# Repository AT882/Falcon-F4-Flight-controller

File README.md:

# Falcon F4 Flight Controller

Custom STM32F405-based flight controller designed for UAV, FPV and aerial robotics applications.

## Overview

The Falcon F4 Flight Controller is a custom-designed flight-control board based on the STM32F405RGT6 ARM Cortex-M4 microcontroller.

The board integrates the core hardware required for a compact UAV flight-control system, including a 6-axis IMU, barometric pressure sensor, analog video OSD, external SPI Flash memory, regulated power supplies, battery-voltage monitoring, current sensing, ESC interfaces, camera and VTX interfaces, USB connectivity and SWD debugging.

The complete electrical schematic is provided in this repository along with images of the designed PCB.

## Hardware Images

### PCB Front View

### PCB Back View

## Key Features

* STM32F405RGT6 ARM Cortex-M4 microcontroller
* ICM-42688-P 6-axis IMU
* BMP388 barometric pressure sensor
* AT7456E analog OSD controller
* W25Q128JV 128-Mbit SPI NOR Flash
* TPS54202DDCR 5 V buck regulator
* XC6206P332MR 3.3 V LDO regulator
* USB Type-C interface
* SWD programming and debugging interface
* Dedicated boot-mode selection
* Multiple ESC signal outputs
* ESC telemetry interface
* Analog camera input
* Analog VTX output
* Battery-voltage monitoring
* Current-sense input
* SPI interfaces
* I²C interface
* Status LEDs
* Power indication
* Dedicated MCU and OSD clock sources

## Main Processing Unit

### STM32F405RGT6

The STM32F405RGT6 is the main processing unit of the Falcon F4.

It provides the processing capability required for real-time flight-control applications and interfaces with the onboard sensors, memory, OSD circuitry, external peripherals and flight-control interfaces.

The MCU provides connections for:

* IMU
* Barometer
* SPI Flash
* OSD
* ESC interfaces
* Battery-voltage monitoring
* Current sensing
* I²C peripherals
* USB
* SWD
* Status LEDs
* Auxiliary GPIO

## Inertial Measurement Unit

### ICM-42688-P

The ICM-42688-P is used as the primary inertial measurement unit.

It provides:

* 3-axis accelerometer
* 3-axis gyroscope

The IMU is connected to the STM32 through an SPI interface.

The main IMU signals are:

```text
SPI1_SCK
SPI1_MISO
SPI1_MOSI
IMU_CS
```

The IMU has local decoupling capacitors to provide a stable supply and reduce supply noise.

The sensor provides motion information required for:

* Attitude estimation
* Angular-rate measurement
* Flight stabilization
* Orientation estimation
* Flight-control algorithms

## Barometric Pressure Sensor

### BMP388

The BMP388 is used for barometric pressure and altitude measurement.

The sensor is connected to the STM32 through the I²C interface.

The primary signals are:

```text
I2C1_SCL
I2C1_SDA
```

The barometer can be used for:

* Altitude estimation
* Altitude hold
* Vertical-position estimation
* Flight stabilization
* Autonomous UAV applications

## On-Screen Display

### AT7456E

The AT7456E is used as the analog video OSD controller.

The OSD section allows flight information to be overlaid onto the analog video stream.

The video path is:

```text
Camera
   |
   v
AV_IN
   |
   v
AT7456E
   |
   v
AV_OUT
   |
   v
VTX
```

The OSD section includes a dedicated 27 MHz crystal and associated circuitry.

Possible OSD information includes:

* Battery voltage
* Flight mode
* Altitude
* Flight status
* Warnings
* Navigation information
* Telemetry information
* Artificial horizon

## External Flash Memory

### W25Q128JV

The W25Q128JV is a 128-Mbit SPI NOR Flash memory device.

The external Flash provides non-volatile memory for storing application data.

Potential uses include:

* Configuration data
* Parameters
* Logging
* Flight data
* Application-specific information

The Flash interface uses:

```text
FLASH_CS
SPI3_SCK
SPI3_MISO
SPI3_MOSI
```

## Power Management

The Falcon F4 contains dedicated power-management circuitry for generating the required voltage rails.

The main power architecture consists of:

```text
+BATT
   |
   +------------------+
   |                  |
   v                  v
5 V Buck          Battery
Regulator         Monitoring
   |
   v
  5 V
   |
   v
3.3 V LDO
   |
   v
 3.3 V
```

## 5 V Regulator

### TPS54202DDCR

The TPS54202DDCR is used as the primary 5 V switching regulator.

The regulator converts the battery input into a regulated 5 V supply.

The regulator section includes:

* TPS54202DDCR
* Inductor
* Input capacitors
* Output capacitors
* Feedback network
* Enable circuitry
* Power flag

The 5 V rail supplies the OSD/video section and other peripherals requiring 5 V.

## 3.3 V Regulator

### XC6206P332MR

The XC6206P332MR provides the 3.3 V supply rail.

The 3.3 V rail powers the main low-voltage digital and sensor circuitry, including:

* STM32F405RGT6
* ICM-42688-P
* BMP388
* W25Q128JV
* Other 3.3 V peripherals

Local decoupling capacitors are provided for the regulator and individual ICs.

## Battery Voltage Monitoring

The Falcon F4 includes an onboard battery-voltage sensing circuit.

A resistor-divider network scales the battery voltage to a suitable level for the STM32 ADC.

The schematic uses:

```text
R18 = 20 kΩ
R19 = 1 kΩ
```

The scaled signal is connected to:

```text
ADC_IN8
```

This allows the flight-control firmware to monitor the connected battery voltage.

Battery-voltage monitoring can be used for:

* Battery status
* Low-voltage warnings
* Battery protection
* Flight telemetry
* Battery monitoring

## Current Monitoring

A dedicated current-sense input is provided.

The signal is labelled:

```text
CURRENT
```

and is connected to the STM32 ADC system.

The current measurement can be used for:

* Current monitoring
* Power-consumption estimation
* Battery monitoring
* Energy-consumption calculation
* Telemetry
* Low-battery management

The actual current-sensor implementation depends on the external ESC or power-monitoring hardware connected to the flight controller.

## ESC Interface

The Falcon F4 provides a dedicated multi-pin ESC interface.

The schematic includes:

```text
ESC_S1
ESC_S2
ESC_S3
ESC_S4
ESC_S5
ESC_S6
ESC_TLM
CURRENT
+BATT
GND
```

The interface is intended to connect the flight controller to external electronic speed controllers.

The multiple ESC signal connections allow the board to be adapted for different multirotor configurations.

The ESC interface can be used for:

* Motor-control signals
* ESC telemetry
* Current monitoring
* Battery monitoring

The exact communication protocol is determined by the flight-control firmware and connected ESC hardware.

## Camera Interface

A dedicated analog camera interface is provided.

The camera connector includes:

```text
GND
+5V
AV_IN
```

The camera video signal is routed to the AT7456E OSD section.

The OSD then overlays flight information onto the video stream before sending it to the VTX.

## VTX Interface

A dedicated VTX connector is provided.

The interface includes:

```text
GND
+BATT
AV_OUT
VTX_TBS
```

The processed analog video signal is available through:

```text
AV_OUT
```

The VTX control signal can be used with compatible video transmitters and firmware.

## USB Type-C Interface

The Falcon F4 includes a USB Type-C connector.

The USB section includes the required USB-C CC resistors and connections to the STM32.

The interface can be used for:

* Firmware development
* Configuration
* Data communication
* Firmware updates
* Development and testing

## Debugging and Programming

### SWD

A dedicated Serial Wire Debug interface is provided for programming and debugging the STM32F405.

The primary SWD signals are:

```text
SWDIO
SWCLK
```

The SWD interface can be used with an ST-LINK or compatible debugger.

It supports:

* Firmware programming
* Breakpoint debugging
* Register inspection
* Memory inspection
* Peripheral debugging
* Hardware bring-up

## Boot Mode

The board includes a dedicated boot-selection circuit.

The schematic provides:

```text
BOOT
BOOT0
```

along with a boot switch and associated pull-down circuitry.

This allows the MCU boot configuration to be selected during development and firmware recovery.

## Status LEDs

The Falcon F4 includes onboard status and power indication LEDs.

The schematic contains:

```text
LED1
LED2
POWER
```

These LEDs can be assigned by firmware to indicate:

* Power status
* Boot status
* Sensor initialization
* Flight-controller state
* Communication status
* Error conditions

## Clock Sources

The board contains dedicated clock sources for the MCU and OSD subsystem.

### MCU Clock

An 8 MHz crystal is provided for the STM32F405 clock system.

### OSD Clock

A separate 27 MHz crystal is provided for the AT7456E OSD controller.

## Communication Interfaces

### SPI

Multiple SPI interfaces are used for high-speed peripheral communication.

The SPI interfaces are used for devices including:

* ICM-42688-P
* W25Q128JV
* Other external peripherals

### I²C

The board provides an I²C interface for peripheral communication.

The primary signals are:

```text
I2C1_SCL
I2C1_SDA
```

The onboard BMP388 is connected through this interface.

## Major Components

| Reference | Component           | Function                      |
| --------- | ------------------- | ----------------------------- |
| U1        | STM32F405RGT6       | Main flight-controller MCU    |
| U2        | BMP388              | Barometric pressure sensor    |
| U3        | ICM-42688-P         | 6-axis IMU                    |
| U4        | W25Q128JV           | 128-Mbit SPI Flash            |
| U5        | TPS54202DDCR        | 5 V buck regulator            |
| U6        | XC6206P332MR        | 3.3 V LDO regulator           |
| IC1       | AT7456E             | Analog OSD controller         |
| Y1        | 27 MHz crystal      | OSD clock source              |
| Y2        | 8 MHz crystal       | MCU clock source              |
| J1        | USB Type-C          | USB interface                 |
| J2        | ESC connector       | ESC interface                 |
| J3        | VTX connector       | VTX interface                 |
| J4        | Camera connector    | Camera interface              |
| J5        | Auxiliary connector | External peripheral interface |
| SW1       | Boot switch         | MCU boot selection            |

## Intended Applications

The Falcon F4 is intended as a hardware platform for:

* FPV drones
* Multirotor UAVs
* Research UAVs
* Autonomous aerial vehicles
* Flight-control development
* UAV research
* Embedded systems development
* UAV education
* Custom flight-control firmware
* Robotics applications
* Experimental aircraft

## Schematic

The complete electrical schematic is provided in this repository.

The schematic contains the major functional sections of the flight controller:

* USB interface
* Battery input
* 5 V power regulation
* 3.3 V regulation
* STM32F405RGT6 MCU
* ICM-42688-P IMU
* BMP388 barometer
* AT7456E OSD
* W25Q128JV Flash
* ESC interface
* Camera interface
* VTX interface
* Battery-voltage sensing
* Current sensing
* SWD interface
* Boot circuit
* Status LEDs
* SPI interfaces
* I²C interface

## Repository Structure

```text
Falcon-F4-Flight-controller/
│
├── README.md
│
├── Schematic/
│   └── Falcon F4 Flightcontroller.kicad_sch
│
└── Images/
    ├── PCB FRONT VIEW.png
    └── PCB BACK VIEW.png
```

## Development Status

Current project status:

**Hardware schematic completed.**

The PCB design has been developed as a custom flight-controller platform based on the STM32F405RGT6.

The repository currently contains the electrical schematic and PCB documentation images.

Further development may include PCB manufacturing files, bill of materials, assembly documentation and firmware.

## Development and Testing

Recommended hardware bring-up sequence:

```text
Schematic Verification
        |
        v
PCB Fabrication
        |
        v
PCB Assembly
        |
        v
Visual Inspection
        |
        v
Power-Rail Verification
        |
        v
STM32 Programming
        |
        v
USB Verification
        |
        v
IMU Verification
        |
        v
Barometer Verification
        |
        v
Flash Verification
        |
        v
OSD and Video Verification
        |
        v
ESC Interface Verification
        |
        v
Flight-Control Firmware
        |
        v
UAV Integration
```

Initial testing should verify:

* Battery input
* 5 V rail
* 3.3 V rail
* MCU operation
* MCU reset
* MCU clock
* USB communication
* SWD communication
* IMU communication
* Barometer communication
* Flash communication
* Battery-voltage ADC measurement
* Current measurement
* ESC outputs
* OSD video input and output

## Safety and Testing Notice

This is a custom flight-controller hardware project.

The hardware should be thoroughly tested before installation on a flight-capable UAV.

Initial testing should be performed without propellers and with appropriate current limiting and laboratory power equipment.

Particular attention should be given to:

* Battery polarity
* Power-rail voltage
* Regulator temperature
* MCU temperature
* Sensor communication
* ADC voltage scaling
* ESC outputs
* Video signal integrity
* Connector polarity
* Short circuits
* PCB assembly quality

## Design Philosophy

The Falcon F4 was designed around four primary objectives.

### Performance

The STM32F405RGT6 provides a capable real-time processing platform suitable for UAV flight-control applications.

### Integration

The board integrates inertial sensing, barometric sensing, OSD, external Flash memory and power regulation into a single custom flight-controller platform.

### Expandability

SPI, I²C, ADC, GPIO and dedicated external connectors provide flexibility for additional sensors, ESCs, cameras, VTX systems and peripherals.

### Development

USB, SWD and BOOT interfaces simplify firmware development, debugging and hardware testing.

## Project Information

| Parameter       | Details                     |
| --------------- | --------------------------- |
| Project Name    | Falcon F4 Flight Controller |
| MCU             | STM32F405RGT6               |
| IMU             | ICM-42688-P                 |
| Barometer       | BMP388                      |
| OSD             | AT7456E                     |
| External Flash  | W25Q128JV                   |
| 5 V Regulator   | TPS54202DDCR                |
| 3.3 V Regulator | XC6206P332MR                |
| PCB Design Tool | KiCad                       |
| Application     | UAV / FPV / Flight Control  |

## License

The licensing terms for the hardware design files and associated documentation will be specified as the project develops.

## Project

Falcon F4 Flight Controller

Custom STM32F405-based flight-control hardware platform for UAV, FPV and aerial robotics applications.

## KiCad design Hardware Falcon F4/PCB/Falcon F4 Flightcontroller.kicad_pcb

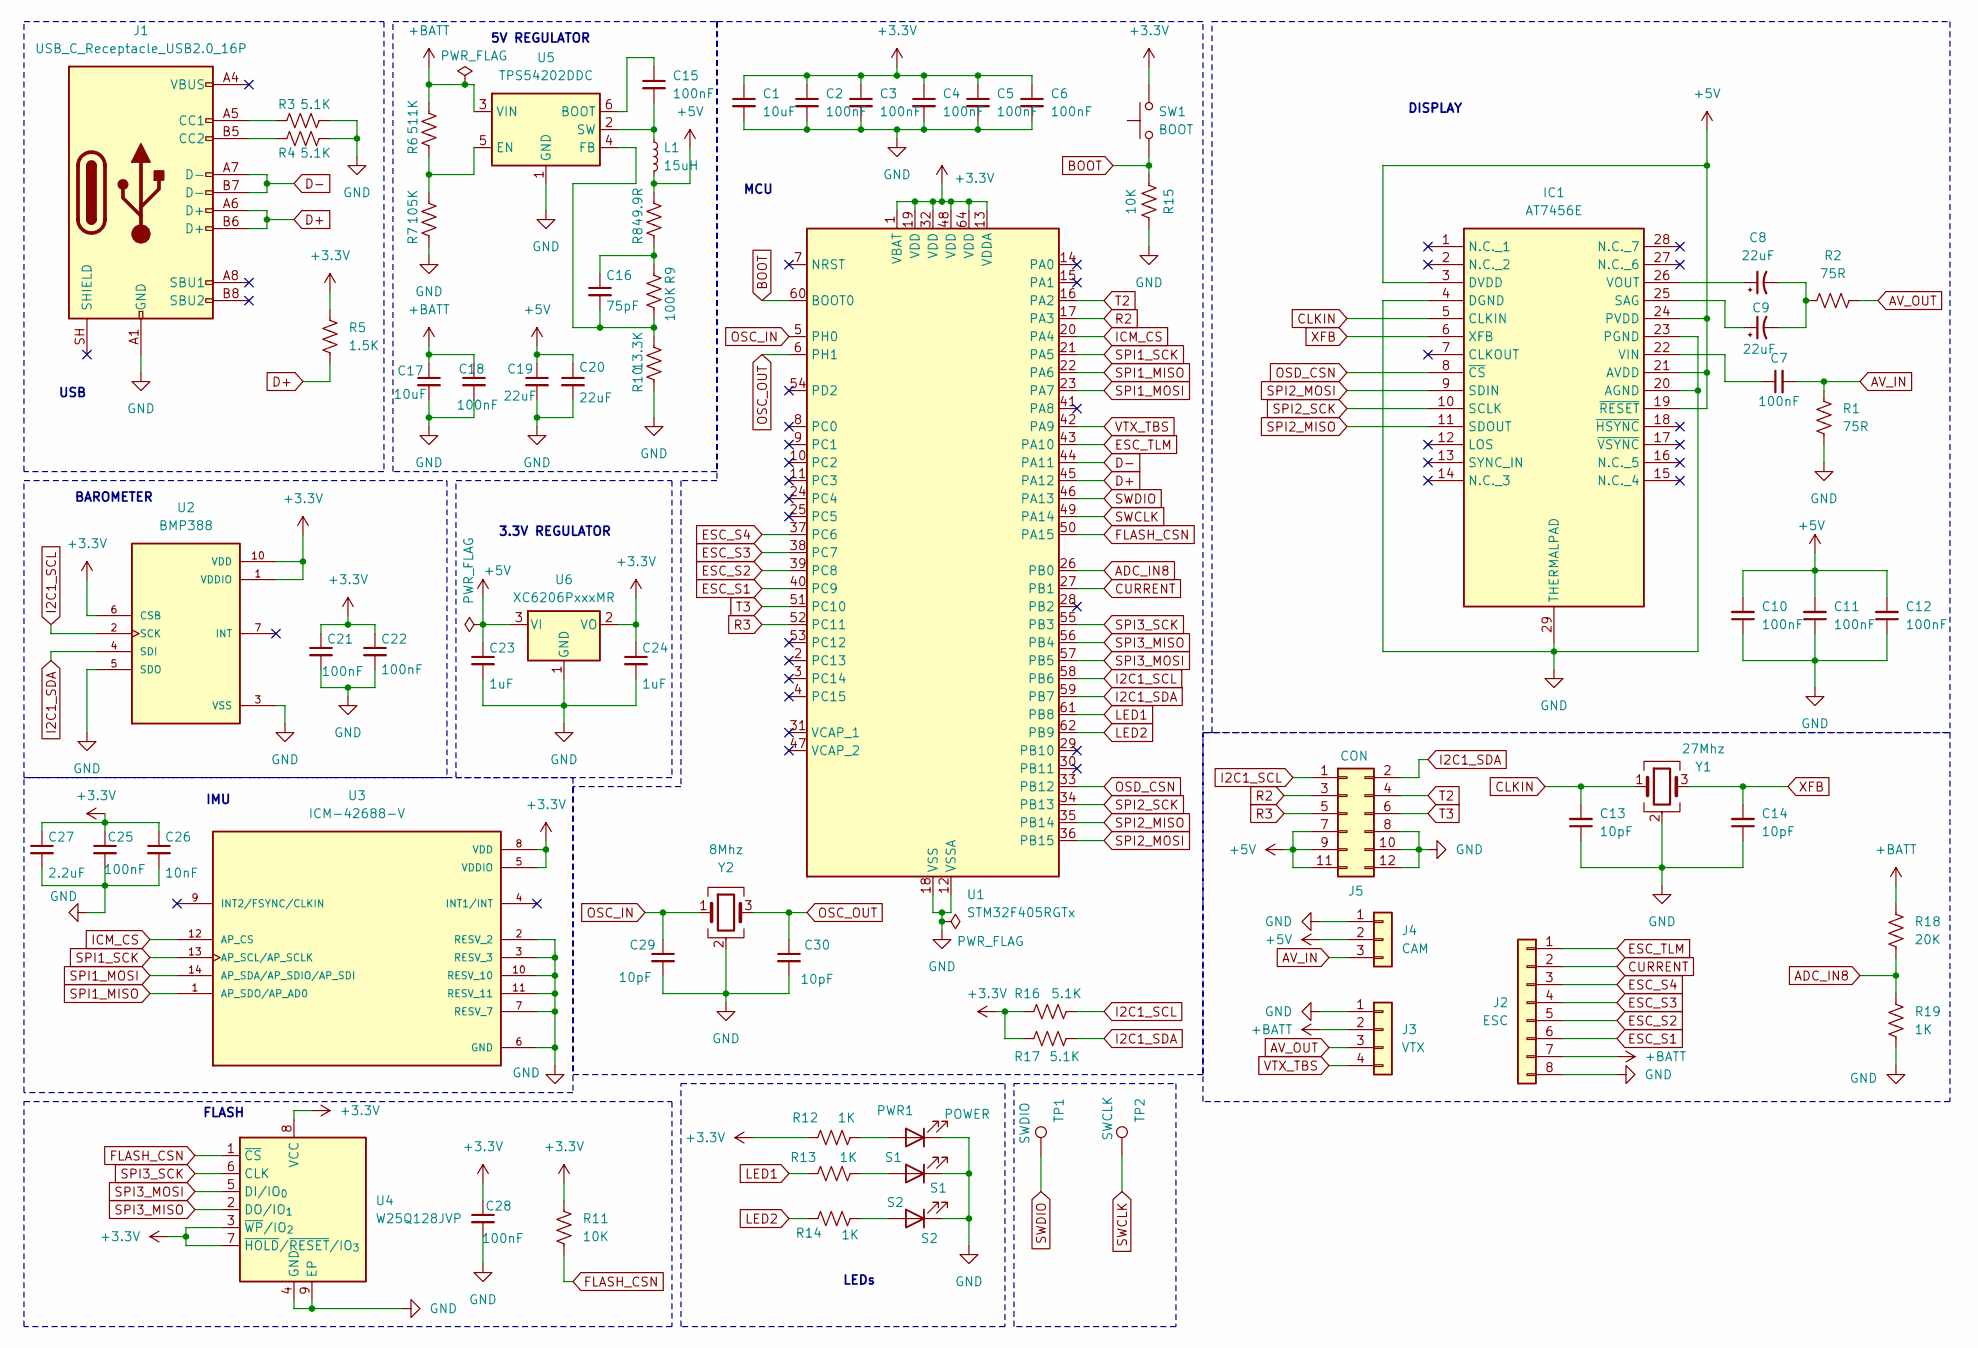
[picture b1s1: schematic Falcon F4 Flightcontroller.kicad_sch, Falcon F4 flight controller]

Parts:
C1: 10uF; C_1206_3216Metric
C2, C3, C4, C5, C6, C7, C10, C11, C12, C15, C18, C21, C22, C25, C28: 100nF; C_0603_1608Metric
C8, C9, C19, C20: 22uF; C_1206_3216Metric
C13, C14, C29, C30: 10pF; C_0603_1608Metric
C16: 75pF; C_0603_1608Metric
C17: 10uF; C_0603_1608Metric
C23, C24: 1uF; C_0603_1608Metric
C26: 10nF; C_0603_1608Metric
C27: 2.2uF; C_0805_2012Metric
IC1: AT7456E; TSSOP-28-1EP_4.4x9.7mm_P0.65mm_EP2.74x4.75mm; Manufacturer_Part_Number AT7456E
J1: USB_C_Receptacle_USB2.0_16P; USB_C_Receptacle_GCT_USB4105-xx-A_16P_TopMnt_Horizontal
J2: ESC; JST_GH_SM08B-GHS-TB_1x08-1MP_P1.25mm_Horizontal
J3: VTX; JST_GH_SM04B-GHS-TB_1x04-1MP_P1.25mm_Horizontal
J4: CAM; JST_GH_SM03B-GHS-TB_1x03-1MP_P1.25mm_Horizontal
J5: CON; PinHeader_2x06_P2.54mm_Vertical
L1: 15uH; L_Coilcraft_LPS3314
PWR1: POWER; LED_0603_1608Metric
R1, R2: 75R; R_0603_1608Metric
R3, R4, R16, R17: 5.1K; R_0603_1608Metric
R5: 1.5K; R_0603_1608Metric
R6: 511K; R_0603_1608Metric
R7: 105K; R_0603_1608Metric
R8: 49.9R; R_0603_1608Metric
R9: 100K; R_0603_1608Metric
R10: 13.3K; R_0603_1608Metric
R11, R15: 10K; R_0603_1608Metric
R12, R13, R14, R19: 1K; R_0603_1608Metric
R18: 20K; R_0603_1608Metric
S1: S1; LED_0603_1608Metric
S2: S2; LED_0603_1608Metric
SW1: BOOT; SW_SPST_TL3305A
TP1: SWDIO; TestPoint_Pad_D1.0mm
TP2: SWCLK; TestPoint_Pad_D1.0mm
U1: STM32F405RGTx; LQFP-64_10x10mm_P0.5mm
U2: BMP388; ST_HLGA-10_2x2mm_P0.5mm_LayoutBorder3x2y; PARTREV 1.7
U3: ICM-42688-V; LGA-14_3x2.5mm_P0.5mm_LayoutBorder3x4y
U4: W25Q128JVP; WSON-8-1EP_6x5mm_P1.27mm_EP3.4x4.3mm
U5: TPS54202DDC; SOT-23-6
U6: XC6206PxxxMR; SOT-23-3
Y1: 27Mhz; Crystal_SMD_3225-4Pin_3.2x2.5mm
Y2: 8Mhz; Crystal_SMD_2520-4Pin_2.5x2.0mm

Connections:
+3.3V: C1.1, C2.1, C3.1, C4.1, C5.1, C6.1, C21.1, C22.1, C24.1, C25.1, C26.1, C27.1, C28.1, R5.2, R11.2, R12.2, R16.2, R17.2, SW1.2, U1.1 (VBAT), U1.13 (VDDA), U1.19 (VDD), U1.32 (VDD), U1.48 (VDD), U1.64 (VDD), U2.1 (VDDIO), U2.6 (CSB), U2.10 (VDD), U3.5 (VDDIO), U3.8 (VDD), U4.3 (~WP/IO_{2}), U4.7 (~HOLD/~RESET/IO_{3}), U4.8 (VCC), U6.2 (VO)
+5V: C10.2, C11.2, C12.2, C19.1, C20.1, C23.1, IC1.3 (DVDD), IC1.19 (~RESET), IC1.21 (AVDD), IC1.24 (PVDD), J4.2, J5.7, J5.9, J5.11, L1.2, R8.2, U6.3 (VI); also elsewhere on the board
+BATT: C17.1, C18.1, J2.7, J3.2, R6.2, R18.1, U5.3 (VIN); also elsewhere on the board
ADC_IN8: R18.2, R19.1, U1.26 (PB0)
AV_IN: C7.2, J4.3, R1.1; also elsewhere on the board
AV_OUT: J3.3, R2.2; also elsewhere on the board
BOOT: R15.2, SW1.1, U1.60 (BOOT0)
CLKIN: C13.2, IC1.5 (CLKIN), Y1.1
CURRENT: J2.2, U1.27 (PB1); also elsewhere on the board
D+: J1.A6 (D+), J1.B6 (D+), R5.1, U1.45 (PA12); also elsewhere on the board
D-: J1.A7 (D-), J1.B7 (D-), U1.44 (PA11); also elsewhere on the board
ESC_S1: J2.6, U1.40 (PC9); also elsewhere on the board
ESC_S2: J2.5, U1.39 (PC8); also elsewhere on the board
ESC_S3: J2.4, U1.38 (PC7); also elsewhere on the board
ESC_S4: J2.3, U1.37 (PC6); also elsewhere on the board
ESC_TLM: J2.1, U1.43 (PA10); also elsewhere on the board
FLASH_CSN: R11.1, U1.50 (PA15), U4.1 (~CS)
GND: C1.2, C2.2, C3.2, C4.2, C5.2, C6.2, C10.1, C11.1, C12.1, C13.1, C14.1, C17.2, C18.2, C19.2, C20.2, C21.2, C22.2, C23.2, C24.2, C25.2, C26.2, C27.2, C28.2, C29.2, C30.2, IC1.4 (DGND), IC1.20 (AGND), IC1.23 (PGND), IC1.29 (THERMALPAD), J1.A1 (GND), J1.A12 (GND), J1.B1 (GND), J1.B12 (GND), J2.8, J3.1, J4.1, J5.8, J5.10, J5.12, PWR1.1 (K), R1.2, R3.2, R4.2, R7.1, R10.1, R15.1, R19.2, S1.1 (K), S2.1 (K), U1.12 (VSSA), U1.18 (VSS), U1.63 (VSS), U2.3 (VSS), U2.5 (SDO), U2.8 (VSS), U2.9 (VSS), U3.2 (RESV_2), U3.3 (RESV_3), U3.6 (GND), U3.7 (RESV_7), U3.10 (RESV_10), U3.11 (RESV_11), U4.4 (GND), U4.9 (EP), U5.1 (GND), U6.1 (GND), Y1.2 (G), Y1.4 (G), Y2.2 (G), Y2.4 (G); also elsewhere on the board
I2C1_SCL: J5.1, R16.1, U1.58 (PB6), U2.2 (SCK)
I2C1_SDA: J5.2, R17.1, U1.59 (PB7), U2.4 (SDI)
ICM_CS: U1.20 (PA4), U3.12 (AP_CS)
LED1: R13.2, U1.61 (PB8)
LED2: R14.2, U1.62 (PB9)
unnamed: C8.2, C9.2, R2.1
unnamed: C16.1, R8.1, R9.1
unnamed: C9.1, IC1.25 (SAG)
unnamed: C7.1, IC1.22 (VIN)
unnamed: C8.1, IC1.26 (VOUT)
unnamed 28: J1.A5 (CC1), R3.1; also elsewhere on the board
unnamed 29: J1.B5 (CC2), R4.1; also elsewhere on the board
unnamed: J1.A4 (VBUS), J1.A9 (VBUS), J1.B4 (VBUS), J1.B9 (VBUS)
unnamed 31: PWR1.2 (A), R12.1; also elsewhere on the board
unnamed: R13.1, S1.2 (A)
unnamed: R14.1, S2.2 (A)
unnamed: C15.1, U5.6 (BOOT)
unnamed: R6.1, R7.2, U5.5 (EN)
unnamed: C16.2, R9.2, R10.2, U5.4 (FB)
unnamed: C15.2, L1.1, U5.2 (SW)
OSC_IN: C29.1, U1.5 (PH0), Y2.1
OSC_OUT: C30.1, U1.6 (PH1), Y2.3
OSD_CSN: IC1.8 (~CS), U1.33 (PB12)
R2: J5.3, U1.17 (PA3)
R3: J5.5, U1.52 (PC11)
SPI1_MISO: U1.22 (PA6), U3.1 (AP_SDO/AP_AD0)
SPI1_MOSI: U1.23 (PA7), U3.14 (AP_SDA/AP_SDIO/AP_SDI)
SPI1_SCK: U1.21 (PA5), U3.13 (AP_SCL/AP_SCLK)
SPI2_MISO: IC1.11 (SDOUT), U1.35 (PB14)
SPI2_MOSI: IC1.9 (SDIN), U1.36 (PB15)
SPI2_SCK: IC1.10 (SCLK), U1.34 (PB13)
SPI3_MISO: U1.56 (PB4), U4.2 (DO/IO_{1})
SPI3_MOSI: U1.57 (PB5), U4.5 (DI/IO_{0})
SPI3_SCK: U1.55 (PB3), U4.6 (CLK)
SWCLK: TP2.1 (1_1), U1.49 (PA14)
SWDIO: TP1.1 (1_1), U1.46 (PA13)
T2: J5.4, U1.16 (PA2)
T3: J5.6, U1.51 (PC10)
VTX_TBS: J3.4, U1.42 (PA9); also elsewhere on the board
XFB: C14.2, IC1.6 (XFB), Y1.3

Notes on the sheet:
3.3V REGULATOR
IMU
MCU
LEDs
USB
BAROMETER
FLASH
5V REGULATOR
DISPLAY

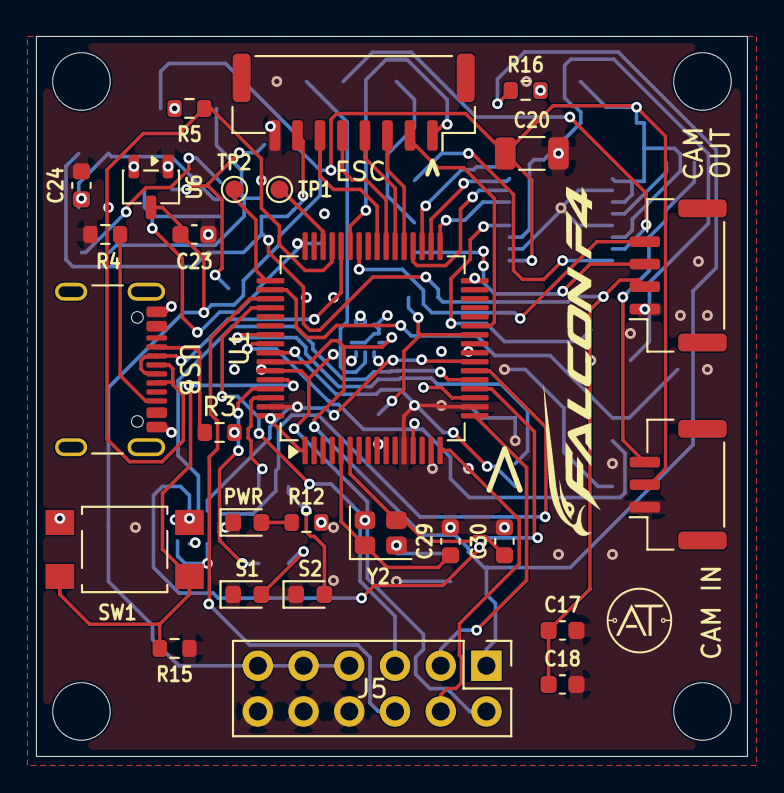
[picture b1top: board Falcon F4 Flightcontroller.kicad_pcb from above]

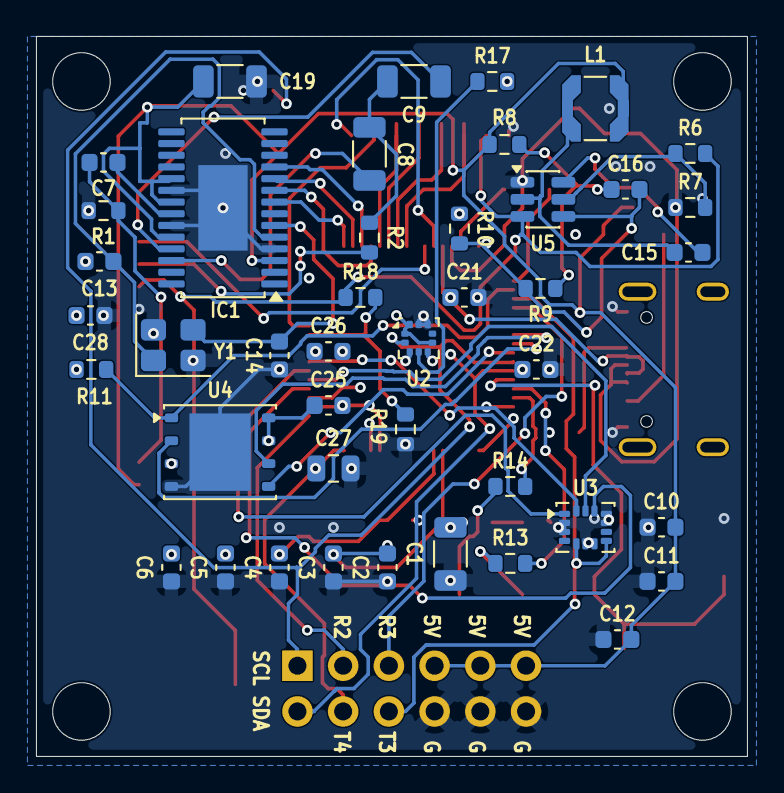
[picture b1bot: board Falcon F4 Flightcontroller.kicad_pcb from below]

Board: 4 copper layers, 39.5 x 40.0 mm, 74 parts (43 on the bottom side), 57 nets.

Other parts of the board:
CAM: VTX; JST_GH_SM04B-GHS-TB_1x04-1MP_P1.25mm_Horizontal
CAM IN: CAM; JST_GH_SM03B-GHS-TB_1x03-1MP_P1.25mm_Horizontal
ESC: ESC; JST_GH_SM08B-GHS-TB_1x08-1MP_P1.25mm_Horizontal
H1, H2, H3, H4: MountingHole_3.2mm_M3
PWR: POWER; LED_0603_1608Metric
USB: USB_C_Receptacle_USB2.0_16P; USB_C_Receptacle_GCT_USB4105-xx-A_16P_TopMnt_Horizontal

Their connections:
+5V: CAM IN.2; also elsewhere on the board
+BATT: CAM.2, ESC.7; also elsewhere on the board
AV_IN: CAM IN.3; also elsewhere on the board
AV_OUT: CAM.3; also elsewhere on the board
CURRENT: ESC.2; also elsewhere on the board
D+: USB.A6 (D+), USB.B6 (D+); also elsewhere on the board
D-: USB.A7 (D-), USB.B7 (D-); also elsewhere on the board
ESC_S1: ESC.6; also elsewhere on the board
ESC_S2: ESC.5; also elsewhere on the board
ESC_S3: ESC.4; also elsewhere on the board
ESC_S4: ESC.3; also elsewhere on the board
ESC_TLM: ESC.1; also elsewhere on the board
GND: CAM.1, CAM IN.1, ESC.8, PWR.1 (K), USB.A1 (GND), USB.A12 (GND), USB.B1 (GND), USB.B12 (GND); also elsewhere on the board
unnamed 28: USB.A5 (CC1); also elsewhere on the board
unnamed 29: USB.B5 (CC2); also elsewhere on the board
unnamed 31: PWR.2 (A); also elsewhere on the board
VTX_TBS: CAM.4; also elsewhere on the board

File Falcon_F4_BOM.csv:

Reference,Qty,Value,Footprint,Datasheet
C1,1,10uF,Capacitor_SMD:C_1206_3216Metric,
"C2,C3,C4,C5,C6,C7,C10,C11,C12,C15,C18,C21,C22,C25,C28",15,100nF,Capacitor_SMD:C_0603_1608Metric,
"C8,C9,C19,C20",4,22uF,Capacitor_SMD:C_1206_3216Metric,
"C13,C14,C29,C30",4,10pF,Capacitor_SMD:C_0603_1608Metric,
C16,1,75pF,Capacitor_SMD:C_0603_1608Metric,
C17,1,10uF,Capacitor_SMD:C_0603_1608Metric,
"C23,C24",2,1uF,Capacitor_SMD:C_0603_1608Metric,
C26,1,10nF,Capacitor_SMD:C_0603_1608Metric,
C27,1,2.2uF,Capacitor_SMD:C_0805_2012Metric,
IC1,1,AT7456E,Package_SO:TSSOP-28-1EP_4.4x9.7mm_P0.65mm_EP2.74x4.75mm,https://datasheet.lcsc.com/szlcsc/ZHONGKEWEI-AT7456E_C82351.pdf
J1,1,USB_C_Receptacle_USB2.0_16P,Connector_USB:USB_C_Receptacle_GCT_USB4105-xx-A_16P_TopMnt_Horizontal,https://www.usb.org/sites/default/files/documents/usb_type-c.zip
J2,1,ESC,Connector_JST:JST_GH_SM08B-GHS-TB_1x08-1MP_P1.25mm_Horizontal,
J3,1,VTX,Connector_JST:JST_GH_SM04B-GHS-TB_1x04-1MP_P1.25mm_Horizontal,
J4,1,CAM,Connector_JST:JST_GH_SM03B-GHS-TB_1x03-1MP_P1.25mm_Horizontal,
J5,1,CON,Connector_PinHeader_2.54mm:PinHeader_2x06_P2.54mm_Vertical,
L1,1,15uH,Inductor_SMD:L_Coilcraft_LPS3314,
PWR1,1,POWER,LED_SMD:LED_0603_1608Metric,
"R1,R2",2,75R,Resistor_SMD:R_0603_1608Metric,
"R3,R4,R16,R17",4,5.1K,Resistor_SMD:R_0603_1608Metric,
R5,1,1.5K,Resistor_SMD:R_0603_1608Metric,
R6,1,511K,Resistor_SMD:R_0603_1608Metric,
R7,1,105K,Resistor_SMD:R_0603_1608Metric,
R8,1,49.9R,Resistor_SMD:R_0603_1608Metric,
R9,1,100K,Resistor_SMD:R_0603_1608Metric,
R10,1,13.3K,Resistor_SMD:R_0603_1608Metric,
"R11,R15",2,10K,Resistor_SMD:R_0603_1608Metric,
"R12,R13,R14,R19",4,1K,Resistor_SMD:R_0603_1608Metric,
R18,1,20K,Resistor_SMD:R_0603_1608Metric,
S1,1,S1,LED_SMD:LED_0603_1608Metric,
S2,1,S2,LED_SMD:LED_0603_1608Metric,
SW1,1,BOOT,Button_Switch_SMD:SW_SPST_TL3305A,
TP1,1,SWDIO,TestPoint:TestPoint_Pad_D1.0mm,
TP2,1,SWCLK,TestPoint:TestPoint_Pad_D1.0mm,
U1,1,STM32F405RGTx,Package_QFP:LQFP-64_10x10mm_P0.5mm,https://www.st.com/resource/en/datasheet/stm32f405rg.pdf
U2,1,BMP388,Package_LGA:ST_HLGA-10_2x2mm_P0.5mm_LayoutBorder3x2y,
U3,1,ICM-42688-V,Package_LGA:LGA-14_3x2.5mm_P0.5mm_LayoutBorder3x4y,
U4,1,W25Q128JVP,Package_SON:WSON-8-1EP_6x5mm_P1.27mm_EP3.4x4.3mm,https://www.winbond.com/resource-files/w25q128jv_dtr%20revc%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
U5,1,TPS54202DDC,Package_TO_SOT_SMD:SOT-23-6,http://www.ti.com/lit/ds/symlink/tps54202.pdf
U6,1,XC6206PxxxMR,Package_TO_SOT_SMD:SOT-23-3,https://www.torexsemi.com/file/xc6206/XC6206.pdf
Y1,1,27Mhz,Crystal:Crystal_SMD_3225-4Pin_3.2x2.5mm,
Y2,1,8Mhz,Crystal:Crystal_SMD_2520-4Pin_2.5x2.0mm,
